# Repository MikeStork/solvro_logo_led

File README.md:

# Solvro Logo PCB

**Solvro Logo PCB** to dekoracyjna płytka PCB w kształcie logo **Strategicznego Koła Naukowego Solvro**.  
Projekt powstał jako element promocyjny oraz demonstracja możliwości projektowania PCB.

---

## Cel projektu

Celem projektu było stworzenie **estetycznej płytki PCB**, która przedstawia logo Solvro i może być używana jako:

- gadżet promocyjny
- demonstracja projektowania PCB
- ozdoba stanowiska pracy
- przykład dla nowych członków sekcji hardware

---

## Projekt

Płytka została zaprojektowana tak, aby **warstwy PCB tworzyły grafikę logo Solvro**.  
Elementy takie jak:

- led
- soldermask
- miedź
- silkscreen

zostały wykorzystane do uzyskania odpowiedniego wyglądu logo.

Projekt pokazuje, że PCB może być używane nie tylko do elektroniki, ale również jako **nośnik grafiki i designu**.

---

## Technologie

Projekt został wykonany przy użyciu:

- **KiCad**
- standardowej technologii **PCB FR4**

---

## Zastosowanie

- materiały promocyjne Solvro  
- przykładowy projekt dla nowych członków sekcji hardware  
- dekoracyjna płytka PCB  

---

## Solvro

Projekt powstał w ramach działań hardware w  
**Strategicznym Kole Naukowym Solvro**.

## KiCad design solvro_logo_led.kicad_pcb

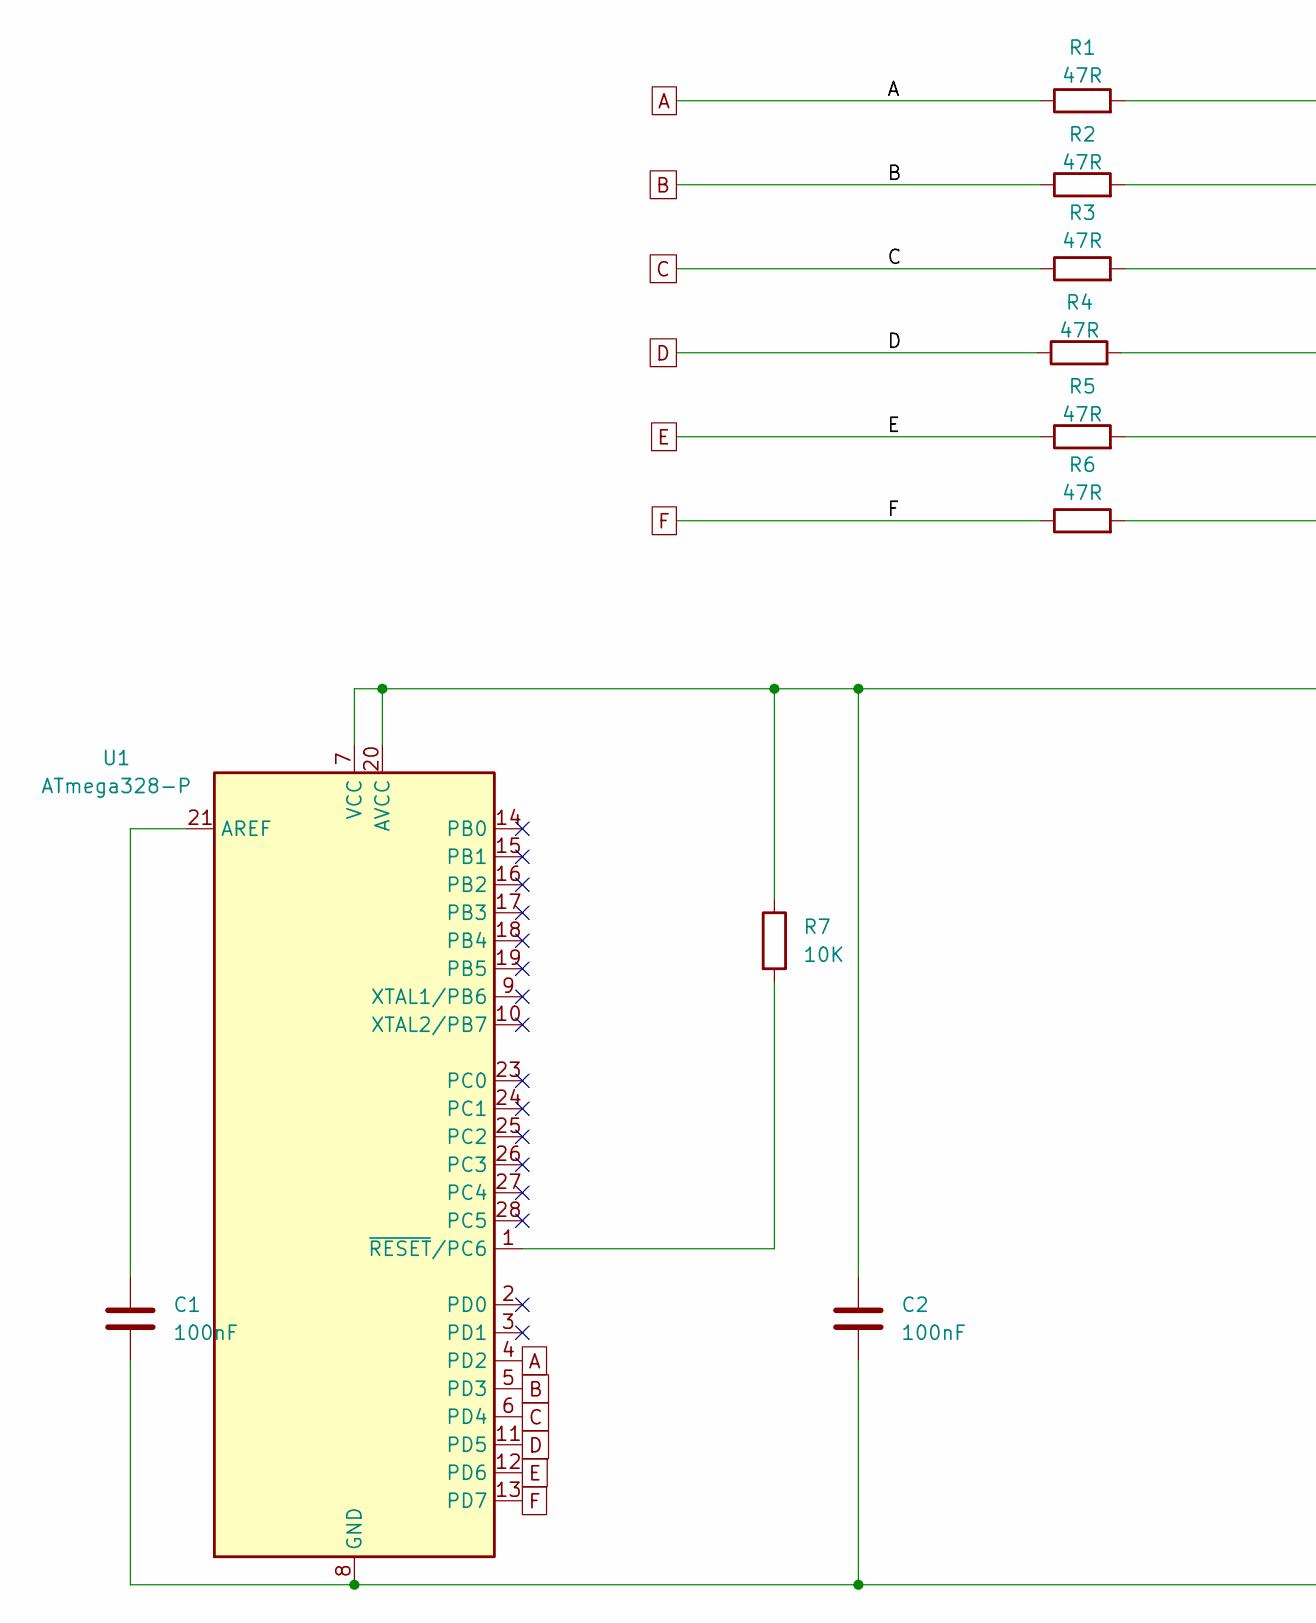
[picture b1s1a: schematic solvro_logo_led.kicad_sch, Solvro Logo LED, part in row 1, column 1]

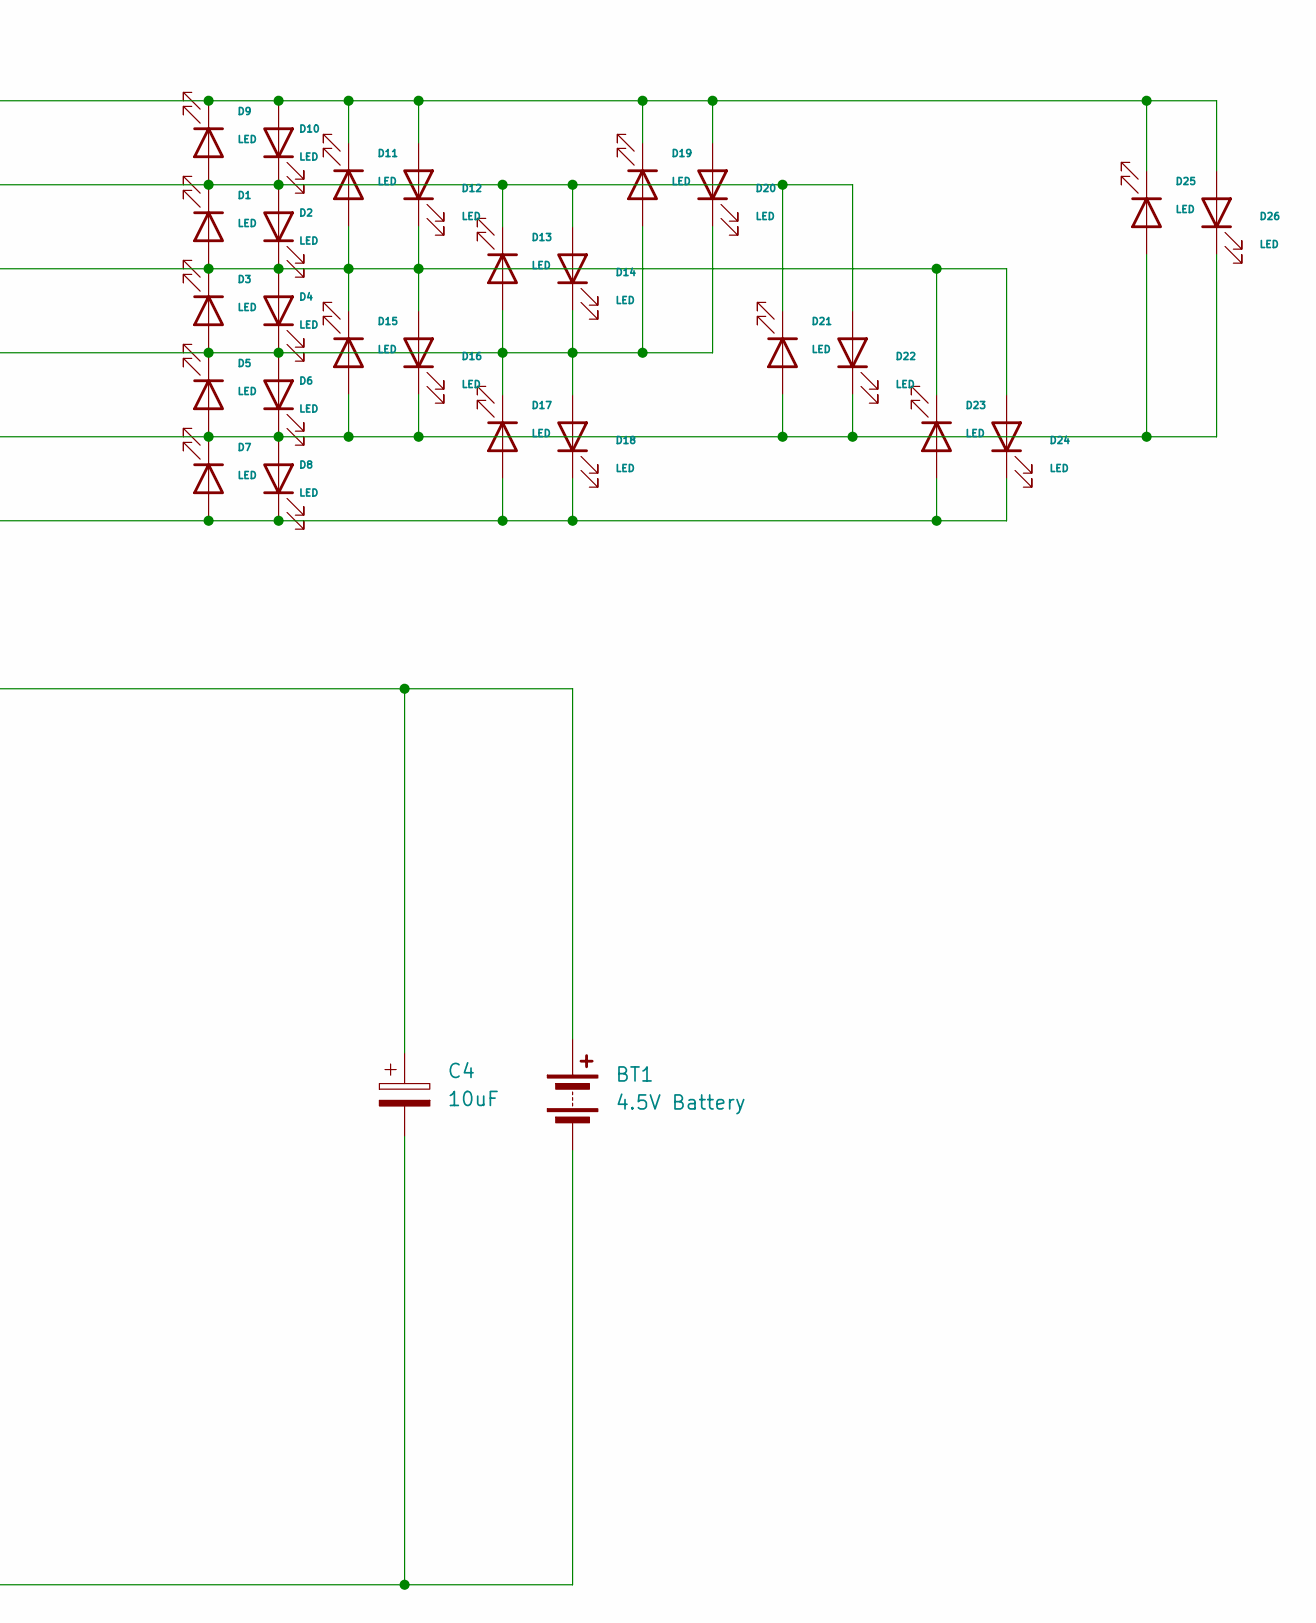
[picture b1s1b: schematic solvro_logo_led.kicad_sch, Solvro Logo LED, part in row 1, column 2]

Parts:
BT1: 4.5V Battery; BatteryHolder_Keystone_2479_3xAAA
C1, C2: 100nF; C_1206_3216Metric_Pad1.33x1.80mm_HandSolder
C4: 10uF; C_1206_3216Metric_Pad1.33x1.80mm_HandSolder
D1, D2, D3, D4, D5, D6, D7, D8, D9, D10, D11, D12, D13, D14, D15, D16, D17, D18, D19, D20, D21, D22, D23, D24, D25, D26: LED; LED_1206_3216Metric_Pad1.42x1.75mm_HandSolder
R1, R2, R3, R4, R5, R6: 47R; R_1206_3216Metric_Pad1.30x1.75mm_HandSolder
R7: 10K; R_1206_3216Metric_Pad1.30x1.75mm_HandSolder
U1: ATmega328-P; DIP-28_W7.62mm

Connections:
A: R1.1, U1.4 (PD2)
B: R2.1, U1.5 (PD3)
C: R3.1, U1.6 (PD4)
D: R4.1, U1.11 (PD5)
E: R5.1, U1.12 (PD6)
F: R6.1, U1.13 (PD7)
unnamed: BT1.1 (+), C2.1, C4.1, R7.1, U1.7 (VCC), U1.20 (AVCC)
unnamed: BT1.2 (-), C1.2, C2.2, C4.2, U1.8 (GND), U1.22 (GND)
unnamed: D1.2 (A), D2.1 (K), D3.1 (K), D4.2 (A), D11.2 (A), D12.1 (K), D15.1 (K), D16.2 (A), D23.1 (K), D24.2 (A), R3.2
unnamed: D1.1 (K), D2.2 (A), D9.2 (A), D10.1 (K), D13.1 (K), D14.2 (A), D21.1 (K), D22.2 (A), R2.2
unnamed: D9.1 (K), D10.2 (A), D11.1 (K), D12.2 (A), D19.1 (K), D20.2 (A), D25.1 (K), D26.2 (A), R1.2
unnamed: D3.2 (A), D4.1 (K), D5.1 (K), D6.2 (A), D13.2 (A), D14.1 (K), D17.1 (K), D18.2 (A), D19.2 (A), D20.1 (K), R4.2
unnamed: D5.2 (A), D6.1 (K), D7.1 (K), D8.2 (A), D15.2 (A), D16.1 (K), D21.2 (A), D22.1 (K), D25.2 (A), D26.1 (K), R5.2
unnamed: D7.2 (A), D8.1 (K), D17.2 (A), D18.1 (K), D23.2 (A), D24.1 (K), R6.2
unnamed: C1.1, U1.21 (AREF)
unnamed: R7.2, U1.1 (~RESET/PC6)

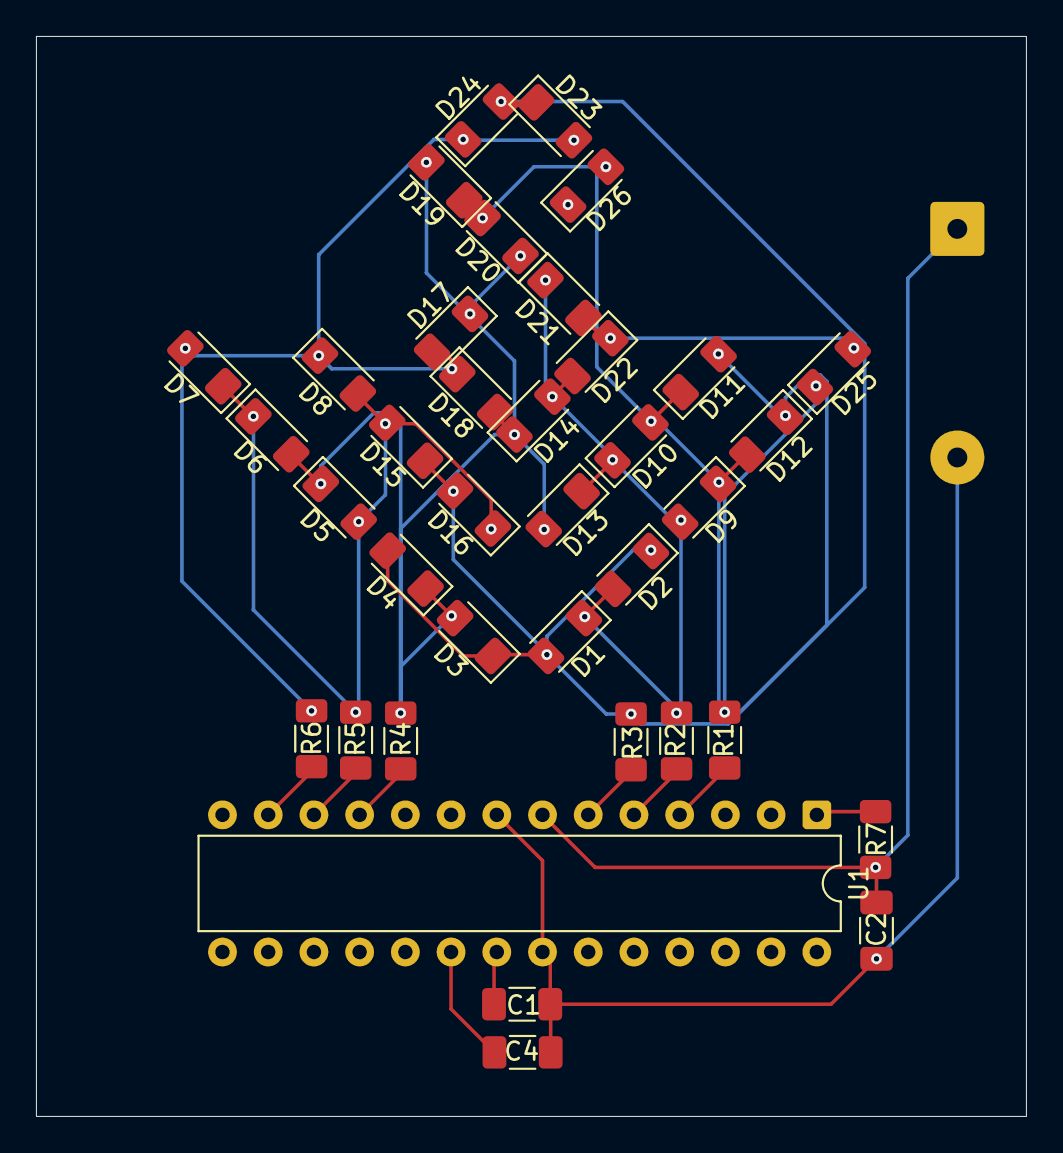
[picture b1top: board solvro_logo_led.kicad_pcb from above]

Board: 2 copper layers, 55.0 x 60.0 mm, 38 parts (1 on the bottom side), 16 nets.

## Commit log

2026-02-21 New PCB repo
2026-02-22 Zmiany rezystorów na ledy
2026-02-22 Added render of all led logo
2026-02-22 Zmiana zasilania na 4.5V
2026-02-22 Dodanie plików gerber, schematu, płytki produkcyjnej i stp
2026-02-22 Dodanie wizualizacji końcowej
2026-03-04 export to gerber
2026-03-14 Add README for Solvro Logo PCB project
    Added a detailed README for the Solvro Logo PCB project, outlining its purpose, design, technologies used, and applications.
2026-03-14 Add visualization image to README
    Added final visualization image to README.
